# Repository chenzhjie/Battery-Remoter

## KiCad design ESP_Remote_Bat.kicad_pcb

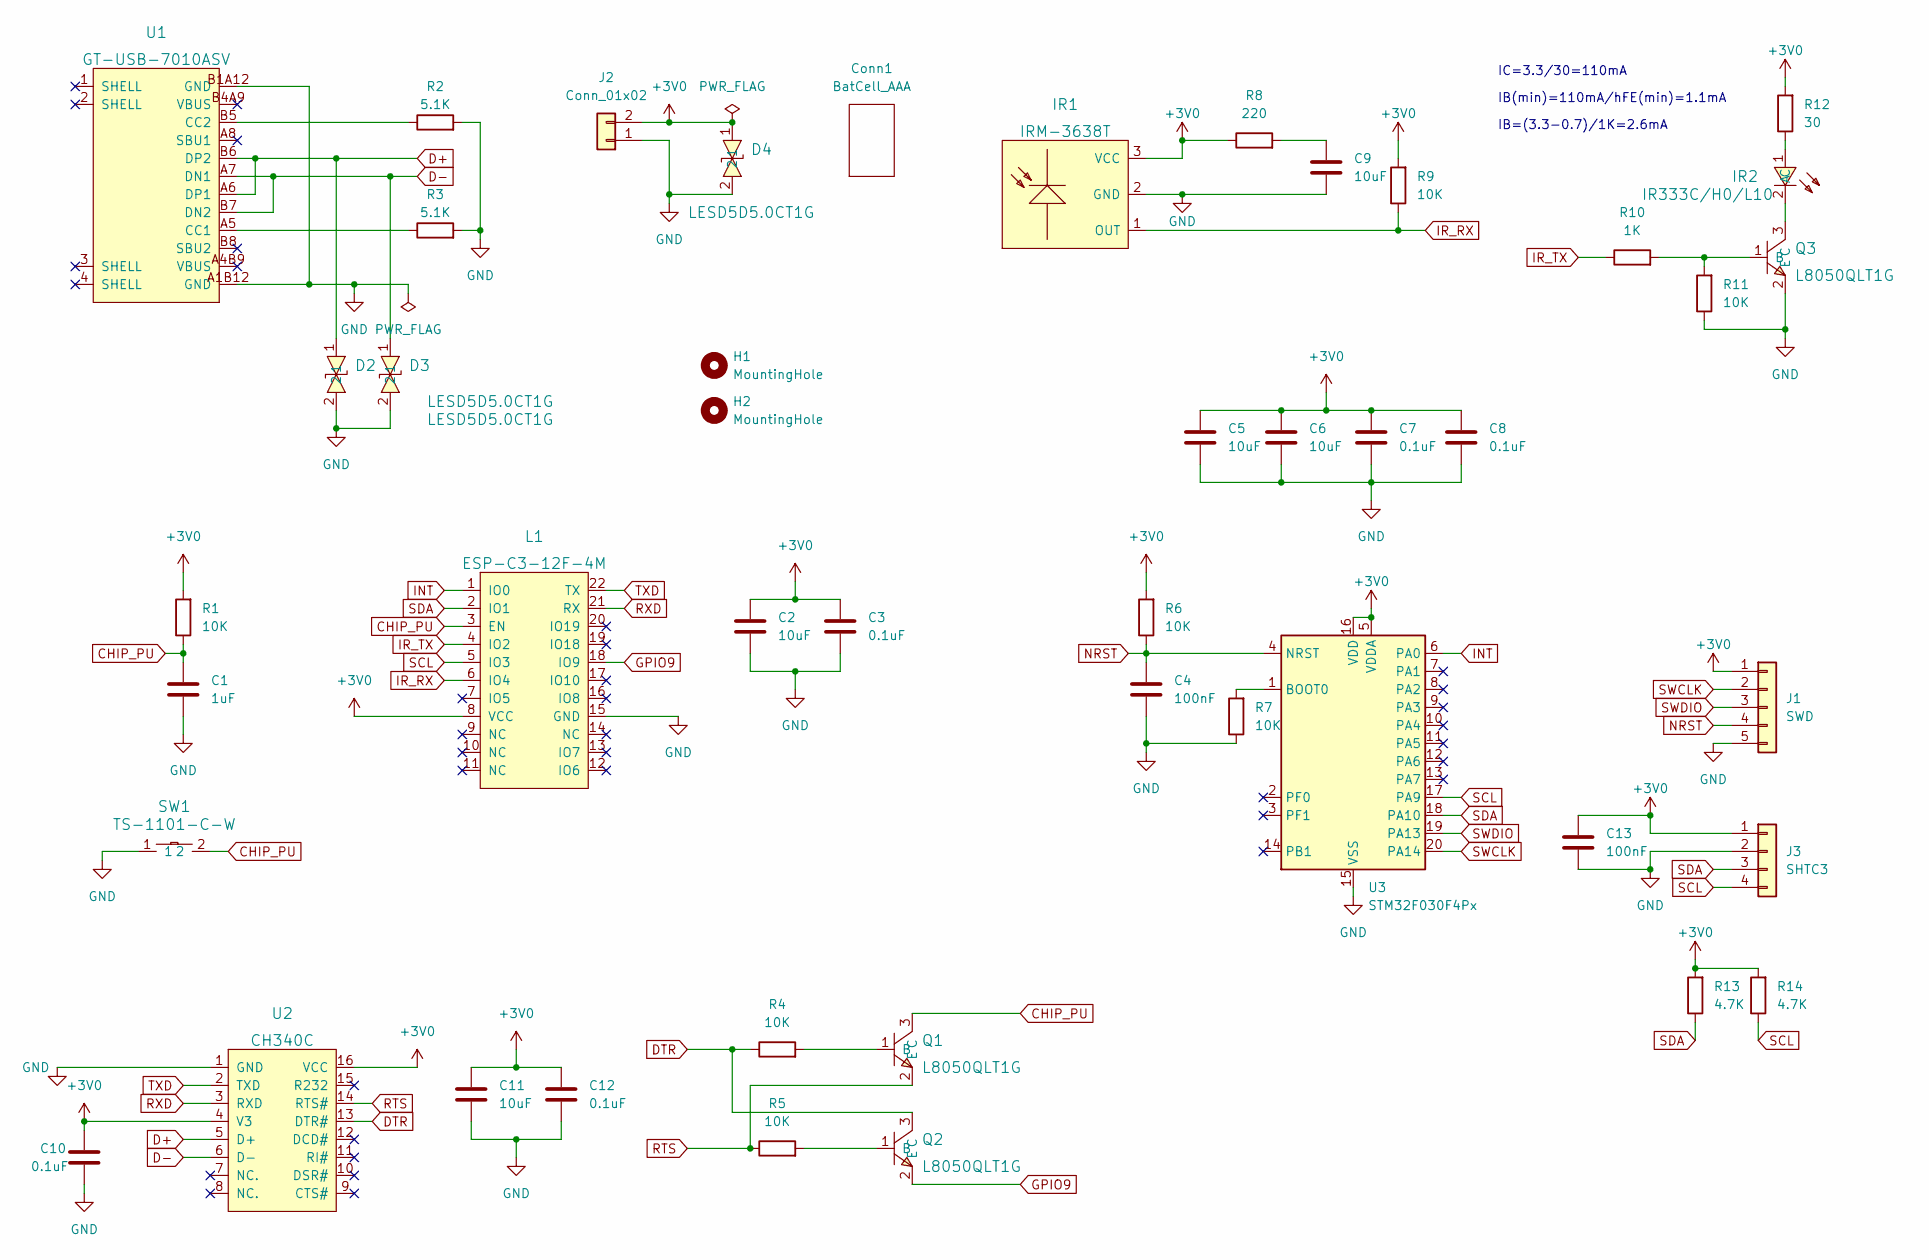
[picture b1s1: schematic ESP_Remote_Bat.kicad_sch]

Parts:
C1: 1uF; C_0603_1608Metric_Pad1.08x0.95mm_HandSolder
C2, C5, C6, C9, C11: 10uF; C_0603_1608Metric_Pad1.08x0.95mm_HandSolder
C3, C7, C8, C10, C12: 0.1uF; C_0603_1608Metric_Pad1.08x0.95mm_HandSolder
C4, C13: 100nF; C_0603_1608Metric_Pad1.08x0.95mm_HandSolder
Conn1: BatCell_AAA
D2, D3, D4: LESD5D5.0CT1G; SOD-523_L1.2-W0.8-LS1.6-BI; LCSC Part C383211
H1, H2: MountingHole; MountingHole_3.2mm_M3
IR1: IRM-3638T; OPTO-TH_IRM-3638T; LCSC Part C16216
IR2: IR333C/H0/L10; LED-TH_BD5.0-P2.54-FD; LCSC Part C72053
J1: SWD; PinHeader_1x05_P2.54mm_Vertical
J2: Conn_01x02; PinHeader_1x02_P2.54mm_Vertical
J3: SHTC3; PinSocket_1x04_P2.54mm_Vertical
L1: ESP-C3-12F-4M; WIRELM-SMD_ESP-C3-12F-2M; LCSC Part C2838647
Q1, Q2, Q3: L8050QLT1G; SOT-23-3_L2.9-W1.3-P1.90-LS2.4-BR; LCSC Part C49581
R1, R4, R5, R6, R7, R9, R11: 10K; R_0603_1608Metric_Pad0.98x0.95mm_HandSolder
R2, R3: 5.1K; R_0603_1608Metric_Pad0.98x0.95mm_HandSolder
R8: 220; R_0603_1608Metric_Pad0.98x0.95mm_HandSolder
R10: 1K; R_0603_1608Metric_Pad0.98x0.95mm_HandSolder
R12: 30; R_0603_1608Metric_Pad0.98x0.95mm_HandSolder
R13, R14: 4.7K; R_0603_1608Metric_Pad0.98x0.95mm_HandSolder
SW1: TS-1101-C-W; SW-SMD_L6.0-W3.3-LS8.0; LCSC Part C318938
U1: GT-USB-7010ASV; USB-C-SMD_G-SWITCH_GT-USB-7010ASV; LCSC Part C2988369
U2: CH340C; SOP-16_L10.0-W3.9-P1.27-LS6.0-BL; LCSC Part C84681
U3: STM32F030F4Px; TSSOP-20_4.4x6.5mm_P0.65mm

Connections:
+3V0: C2.1, C3.1, C5.1, C6.1, C7.1, C8.1, C10.1, C11.1, C12.1, C13.1, D4.1, IR1.3 (VCC), J1.1, J2.2, J3.1, L1.8 (VCC), R1.2, R6.2, R8.1, R9.2, R12.2, R13.2, R14.2, U2.4 (V3), U2.16 (VCC), U3.5 (VDDA), U3.16 (VDD)
CHIP_PU: C1.1, L1.3 (EN), Q1.3 (C), R1.1, SW1.2
D+: D2.1, U1.A6 (DP1), U1.B6 (DP2), U2.5 (D+)
D-: D3.1, U1.A7 (DN1), U1.B7 (DN2), U2.6 (D-)
DTR: Q2.3 (C), R4.1, U2.13 (DTR#)
GND: C1.2, C2.2, C3.2, C4.2, C5.2, C6.2, C7.2, C8.2, C9.2, C10.2, C11.2, C12.2, C13.2, D2.2, D3.2, D4.2, IR1.2 (GND), J1.5, J2.1, J3.2, L1.15 (GND), Q3.2 (E), R2.2, R3.2, R7.1, R11.1, SW1.1, U1.A1B12 (GND), U1.B1A12 (GND), U2.1 (GND), U3.15 (VSS)
GPIO9: L1.18 (IO9), Q2.2 (E)
INT: L1.1 (IO0), U3.6 (PA0)
IR_RX: IR1.1 (OUT), L1.6 (IO4), R9.1
IR_TX: L1.4 (IO2), R10.1
NRST: C4.1, J1.4, R6.1, U3.4 (NRST)
unnamed: C9.1, R8.2
unnamed: IR2.1 (A), R12.1
unnamed: IR2.2 (C), Q3.3 (C)
unnamed: Q1.1 (B), R4.2
unnamed: Q2.1 (B), R5.2
unnamed: Q3.1 (B), R10.2, R11.2
unnamed: R2.1, U1.B5 (CC2)
unnamed: R3.1, U1.A5 (CC1)
unnamed: R7.2, U3.1 (BOOT0)
RTS: Q1.2 (E), R5.1, U2.14 (RTS#)
RXD: L1.21 (RX), U2.3 (RXD)
SCL: J3.4, L1.5 (IO3), R14.1, U3.17 (PA9)
SDA: J3.3, L1.2 (IO1), R13.1, U3.18 (PA10)
SWCLK: J1.2, U3.20 (PA14)
SWDIO: J1.3, U3.19 (PA13)
TXD: L1.22 (TX), U2.2 (TXD)

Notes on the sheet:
IC=3.3/30=110mA
IB(min)=110mA/hFE(min)=1.1mA
IB=(3.3-0.7)/1K=2.6mA

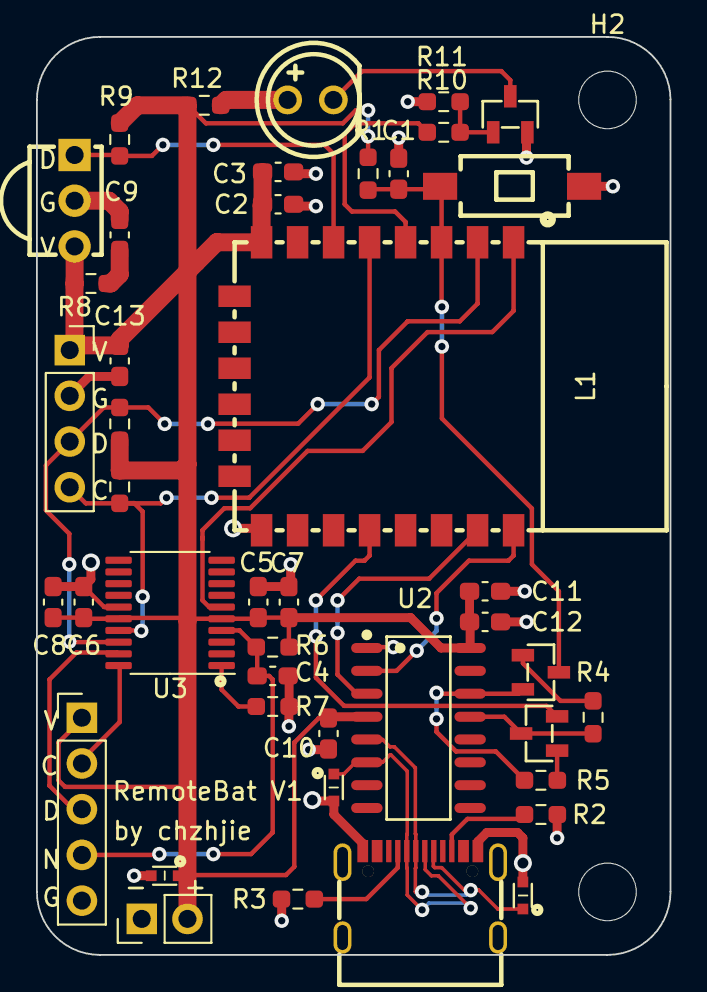
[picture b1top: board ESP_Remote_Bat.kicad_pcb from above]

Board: 2 copper layers, 35.2 x 51.0 mm, 46 parts (1 on the bottom side), 27 nets.

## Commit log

2022-08-14 init
